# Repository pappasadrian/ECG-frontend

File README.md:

# ECG-frontend
ECG frontend PCB schematic, using an AD8232 IC

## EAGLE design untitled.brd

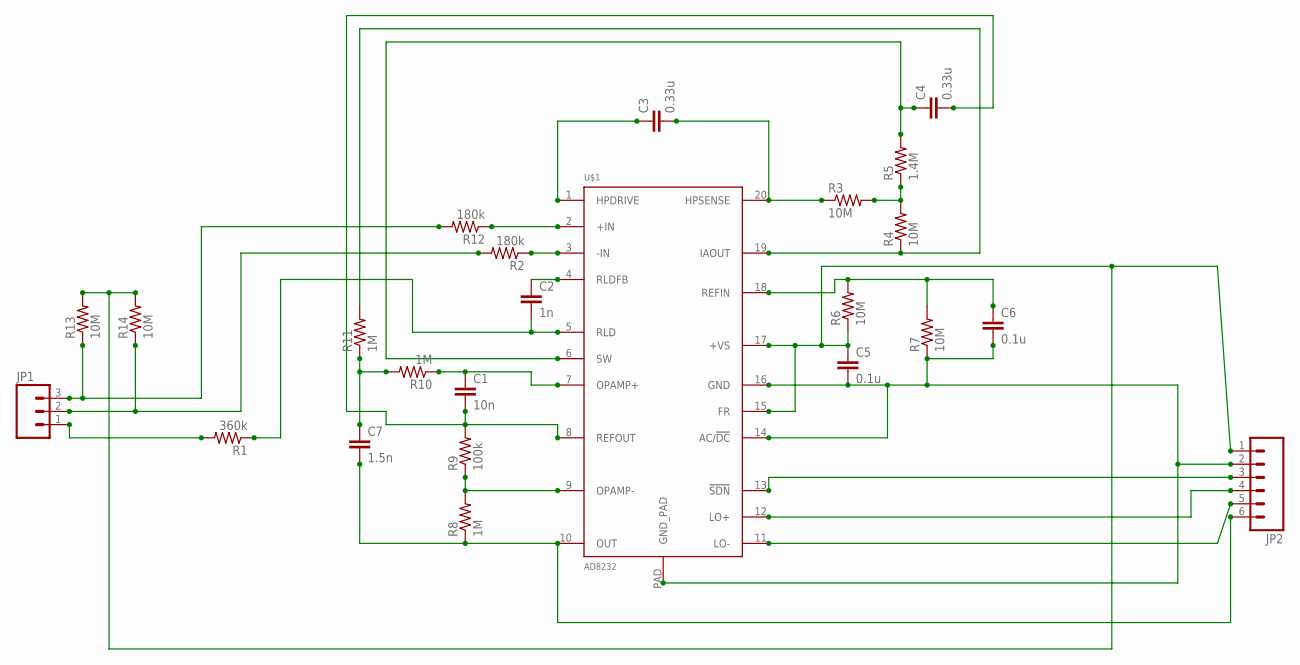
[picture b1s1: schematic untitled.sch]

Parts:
C1: 10n; C0603
C2: 1n; C0603
C3, C4: 0.33u; C0603
C5, C6: 0.1u; C0603
C7: 1.5n; C0603
JP1: M03PTH; 1X03
JP2: M06SILK_FEMALE_PTH; 1X06
R1: 360k; R0603
R2, R12: 180k; R0603
R3, R4, R6, R7, R13, R14: 10M; R0603
R5: 1.4M; R0603
R8, R10, R11: 1M; R0603
R9: 100k; R0603
U$1: AD8232; LFCSP_20

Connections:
unnamed: C3.1, U$1.1 (HPDRIVE)
unnamed: C3.2, R3.1, U$1.20 (HPSENSE)
unnamed: R3.2, R4.2, R5.1
unnamed: C4.1, R5.2, U$1.6 (SW)
unnamed: R4.1, R11.2, U$1.19 (IAOUT)
unnamed: C6.1, R6.2, R7.2, U$1.18 (REFIN)
unnamed: JP2.5, U$1.11 (LO-)
unnamed: C5.2, C6.2, JP2.2, R7.1, U$1.14 (AC/!DC), U$1.16 (GND), U$1.PAD (GND_PAD)
unnamed: JP2.4, U$1.12 (LO+)
unnamed: JP2.3, U$1.13 (!SDN)
unnamed: C7.2, JP2.6, R8.1, U$1.10 (OUT)
unnamed: C7.1, R10.2, R11.1
unnamed: C1.1, R10.1, U$1.7 (OPAMP+)
unnamed: C1.2, C4.2, R9.2, U$1.8 (REFOUT)
unnamed: R8.2, R9.1, U$1.9 (OPAMP-)
unnamed: C2.1, U$1.4 (RLDFB)
unnamed: JP1.1, R1.2
unnamed: R2.1, U$1.3 (-IN)
unnamed: R12.1, U$1.2 (+IN)
unnamed: JP1.3, R12.2, R13.1
unnamed: JP1.2, R2.2, R14.1
unnamed: C5.1, JP2.1, R6.1, R13.2, R14.2, U$1.15 (FR), U$1.17 (+VS)
unnamed: C2.2, R1.1, U$1.5 (RLD)

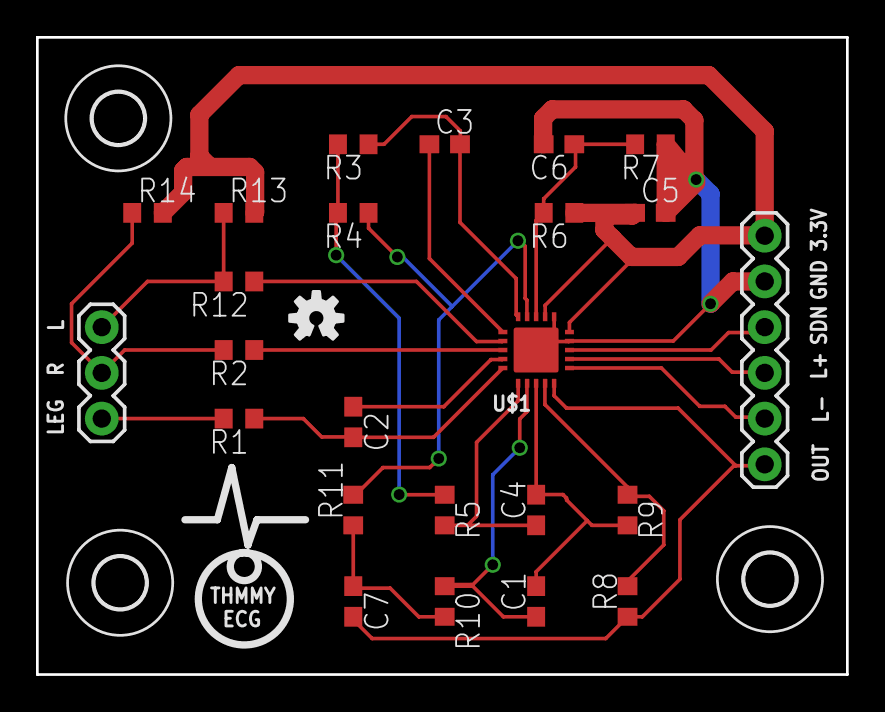
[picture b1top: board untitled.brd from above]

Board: 2 copper layers, 45.0 x 35.4 mm, 28 parts (0 on the bottom side), 23 nets.

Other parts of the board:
U$2, U$3, U$4: 2,8
U$6: OSHW-LOGO-S

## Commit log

2015-06-24 initial project upload

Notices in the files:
parts and their libraries:
SparkFun-Connectors: Licensing: Creative Commons ShareAlike 4.0 International - https://creativecommons.org/licenses/by-sa/4.0
